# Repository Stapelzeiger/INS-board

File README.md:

INS-board
=========
This is a compact inertial navigation system (INS) board.
It is used as an autopilot for quad-copters and fixed wing aircrafts.

Main features:
-------------
 - 3-axis gyroscope
 - Two 3-axis accelerometers (one for low g and one for high g accelerations)
 - 3-axis magnetometer
 - Barometer
 - ARM controller with FPU
 - microSD card
 - USB
 - 1x CAN
 - 4x UARTs
 - 1x I2C

Finished board
--------------

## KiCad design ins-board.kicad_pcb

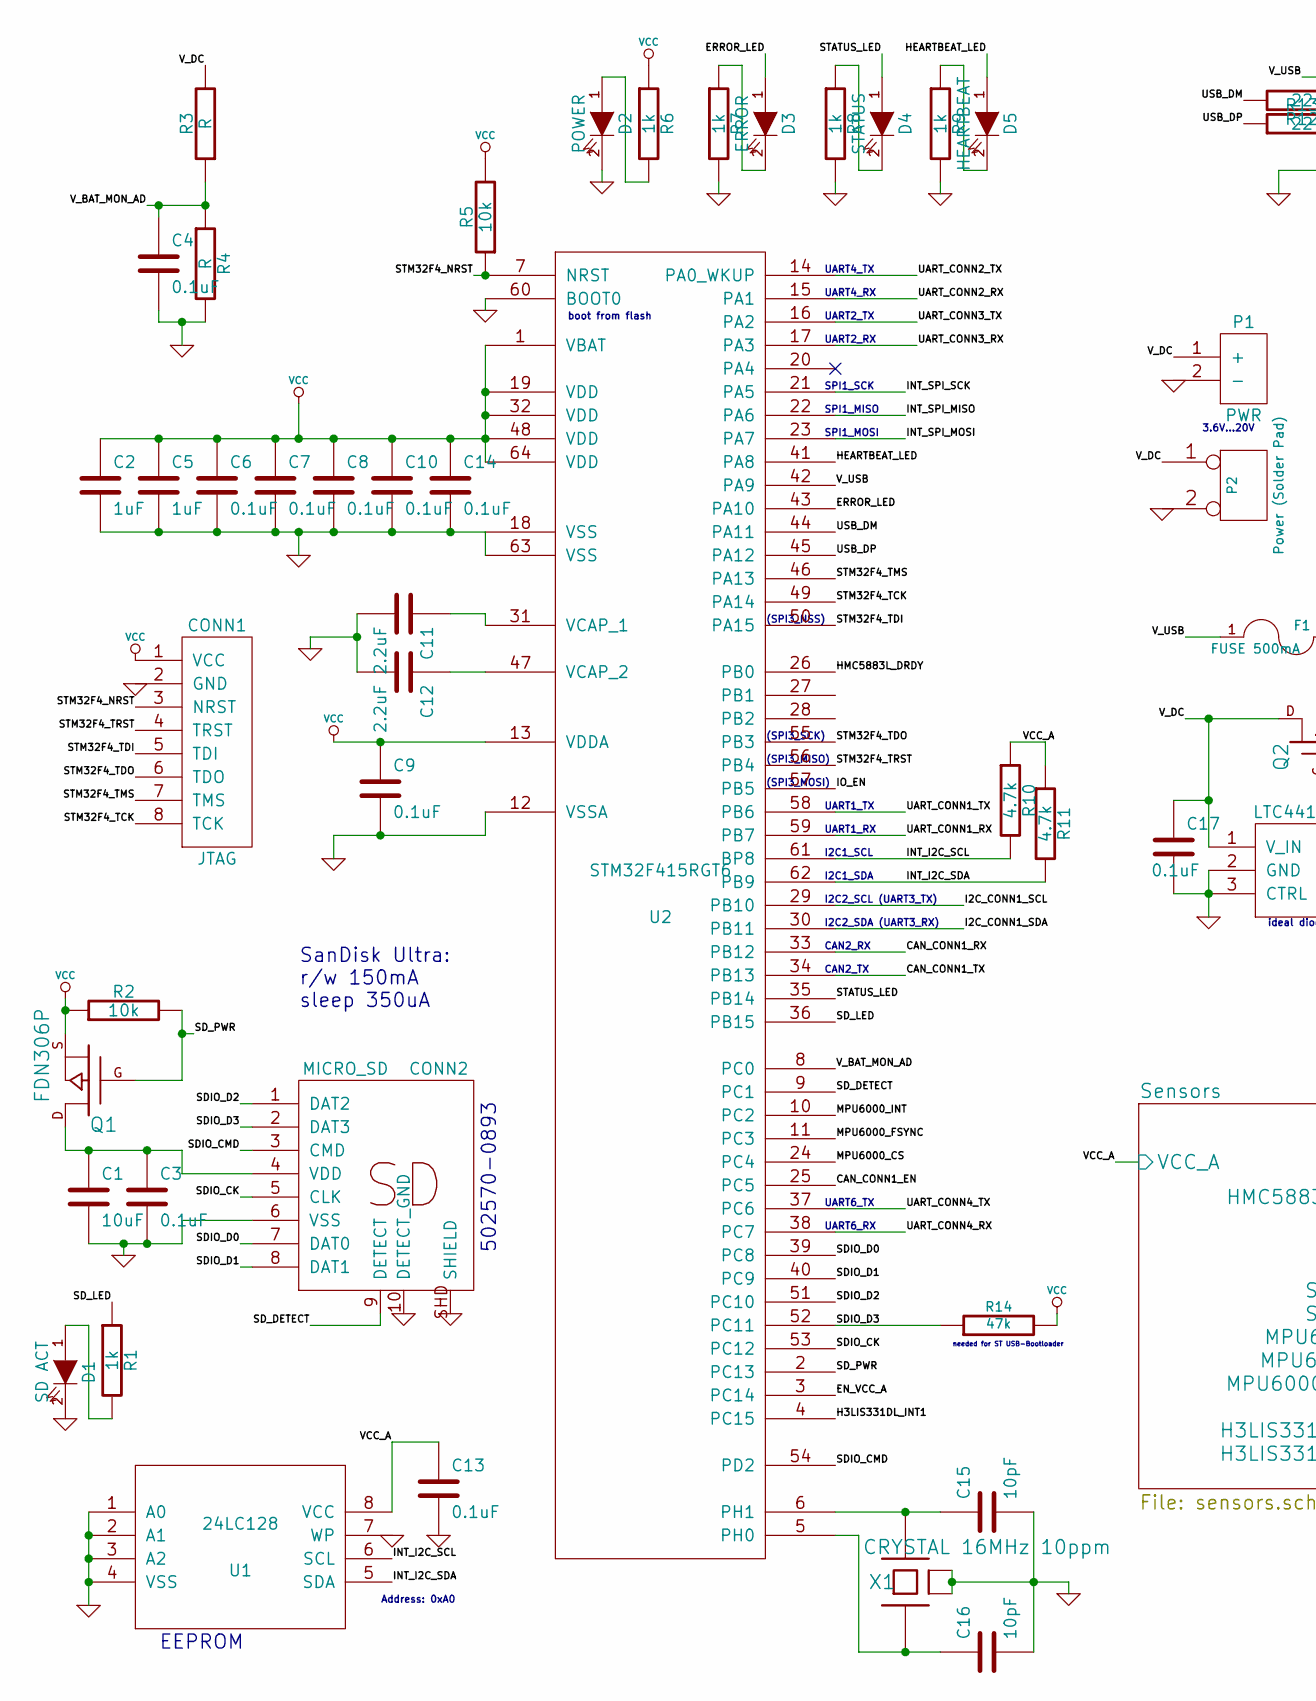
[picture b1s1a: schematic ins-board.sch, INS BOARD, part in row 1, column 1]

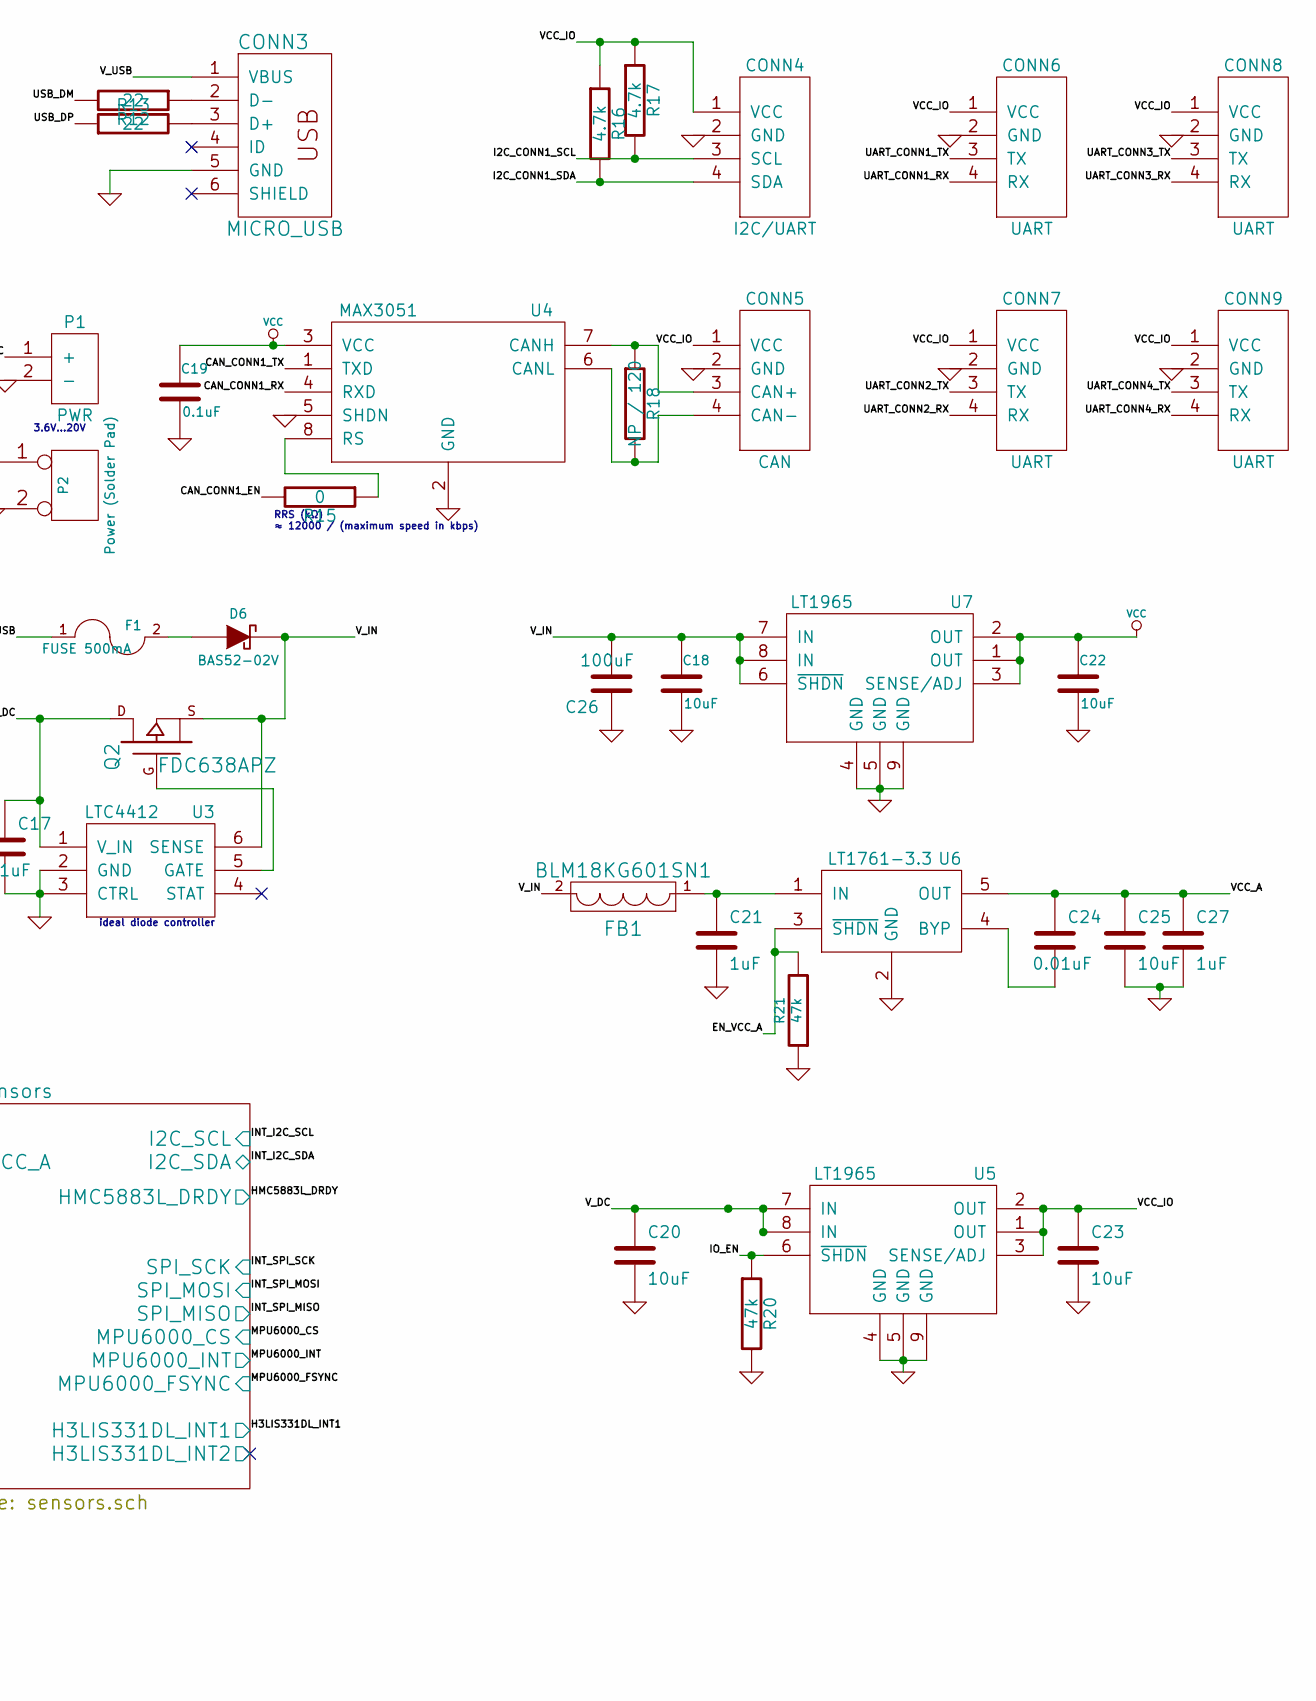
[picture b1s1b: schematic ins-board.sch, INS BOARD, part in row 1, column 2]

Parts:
C1, C20, C23, C25: 10uF
C2, C5, C21, C27: 1uF
C3, C4, C6, C7, C8, C9, C10, C13, C14, C17: 0.1uF
C11, C12: 2.2uF
C15, C16: 10pF
C18, C22: 10uF
C19: 0.1uF
C24: 0.01uF
C26: 100uF; PartNum EMK325ABJ107MM-T
CONN1: JTAG; MODULE
CONN2: MICRO_SD; MODULE
CONN3: MICRO_USB
CONN4: I2C/UART; MODULE
CONN5: CAN; MODULE
CONN6, CONN7, CONN8, CONN9: UART; MODULE
D1: SD ACT
D2: POWER
D3: ERROR
D4: STATUS
D5: HEARTBEAT
D6: BAS52-02V
F1: FUSE 500mA
FB1: BLM18KG601SN1
P1: PWR; MODULE
P2: Power (Solder Pad)
Q1: FDN306P
Q2: FDC638APZ
R1, R6, R7, R8, R9: 1k
R2, R5: 10k
R3, R4: R
R10, R11, R16, R17: 4.7k
R12, R13: 22
R14, R21: 47k
R15: 0
R18: NP / 120
R20: 47k
U1: 24LC128; MODULE
U2: STM32F415RGT6; MODULE
U3: LTC4412; MODULE
U4: MAX3051; MODULE
U5, U7: LT1965; MODULE
U6: LT1761-3.3; MODULE
X1: CRYSTAL 16MHz 10ppm

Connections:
/CAN_CONN1_EN: R15.2, U2.25 (PC5)
/CAN_CONN1_RX: U2.33 (PB12), U4.4 (RXD)
/CAN_CONN1_TX: U2.34 (PB13), U4.1 (TXD)
/EN_VCC_A: R21.2, U2.3 (PC14), U6.3 (~SHDN)
/ERROR_LED: D3.1 (A), U2.43 (PA10)
/HEARTBEAT_LED: D5.1 (A), U2.41 (PA8)
/I2C_CONN1_SCL: CONN4.3 (SCL), R17.2, U2.29 (PB10)
/I2C_CONN1_SDA: CONN4.4 (SDA), R16.2, U2.30 (PB11)
/IO_EN: R20.1, U2.57 (PB5), U5.6 (~SHDN)
/SDIO_CK: CONN2.5 (CLK), U2.53 (PC12)
/SDIO_CMD: CONN2.3 (CMD), U2.54 (PD2)
/SDIO_D0: CONN2.7 (DAT0), U2.39 (PC8)
/SDIO_D1: CONN2.8 (DAT1), U2.40 (PC9)
/SDIO_D2: CONN2.1 (DAT2), U2.51 (PC10)
/SDIO_D3: CONN2.2 (DAT3), R14.1, U2.52 (PC11)
/SD_DETECT: CONN2.9 (DETECT), U2.9 (PC1)
/SD_LED: R1.1, U2.36 (PB15)
/SD_PWR: Q1.G, R2.2, U2.2 (PC13)
/STATUS_LED: D4.1 (A), U2.35 (PB14)
/STM32F4_NRST: CONN1.3 (NRST), R5.1, U2.7 (NRST)
/STM32F4_TCK: CONN1.8 (TCK), U2.49 (PA14)
/STM32F4_TDI: CONN1.5 (TDI), U2.50 (PA15)
/STM32F4_TDO: CONN1.6 (TDO), U2.55 (PB3)
/STM32F4_TMS: CONN1.7 (TMS), U2.46 (PA13)
/STM32F4_TRST: CONN1.4 (TRST), U2.56 (PB4)
/Sensors/H3LIS331DL_INT1: U2.4 (PC15); also elsewhere on the board
/Sensors/HMC5883L_DRDY: U2.26 (PB0); also elsewhere on the board
/Sensors/I2C_SCL: R10.2, U1.6 (SCL), U2.61 (BP8); also elsewhere on the board
/Sensors/I2C_SDA: R11.2, U1.5 (SDA), U2.62 (PB9); also elsewhere on the board
/Sensors/MPU6000_CS: U2.24 (PC4); also elsewhere on the board
/Sensors/MPU6000_FSYNC: U2.11 (PC3); also elsewhere on the board
/Sensors/MPU6000_INT: U2.10 (PC2); also elsewhere on the board
/Sensors/SPI_MISO: U2.22 (PA6); also elsewhere on the board
/Sensors/SPI_MOSI: U2.23 (PA7); also elsewhere on the board
/Sensors/SPI_SCK: U2.21 (PA5); also elsewhere on the board
/Sensors/VCC_A: C13.1, C24.1, C25.1, C27.1, R10.1, R11.1, U1.8 (VCC), U6.5 (OUT); also elsewhere on the board
/UART_CONN1_RX: CONN6.4 (RX), U2.59 (PB7)
/UART_CONN1_TX: CONN6.3 (TX), U2.58 (PB6)
/UART_CONN2_RX: CONN7.4 (RX), U2.15 (PA1)
/UART_CONN2_TX: CONN7.3 (TX), U2.14 (PA0_WKUP)
/UART_CONN3_RX: CONN8.4 (RX), U2.17 (PA3)
/UART_CONN3_TX: CONN8.3 (TX), U2.16 (PA2)
/UART_CONN4_RX: CONN9.4 (RX), U2.38 (PC7)
/UART_CONN4_TX: CONN9.3 (TX), U2.37 (PC6)
/USB_DM: R12.2, U2.44 (PA11)
/USB_DP: R13.1, U2.45 (PA12)
/VCC_IO: C23.1, CONN4.1 (VCC), CONN5.1 (VCC), CONN6.1 (VCC), CONN7.1 (VCC), CONN8.1 (VCC), CONN9.1 (VCC), R16.1, R17.1, U5.1 (OUT), U5.2 (OUT), U5.3 (SENSE/ADJ)
/V_BAT_MON_AD: C4.1, R3.1, R4.1, U2.8 (PC0)
/V_DC: C17.1, C20.1, P1.1 (+), P2.1, Q2.D, R3.2, U3.1 (V_IN), U5.7 (IN), U5.8 (IN)
/V_IN: C18.1, C26.2, D6.2 (K), FB1.2, Q2.S, U3.6 (SENSE), U7.6 (~SHDN), U7.7 (IN), U7.8 (IN)
/V_USB: CONN3.1 (VBUS), F1.1, U2.42 (PA9)
GND: C1.2, C2.2, C3.2, C4.2, C5.2, C6.2, C7.2, C8.2, C9.2, C10.2, C11.2, C12.2, C13.2, C14.2, C15.2, C16.2, C17.2, C18.2, C19.2, C20.2, C21.2, C22.2, C23.2, C25.2, C26.1, C27.2, CONN1.2 (GND), CONN1.MECH (GND), CONN2.6 (VSS), CONN2.10 (DETECT_GND), CONN2.SHD (SHIELD), CONN3.5 (GND), CONN4.2 (GND), CONN4.MECH (GND), CONN5.2 (GND), CONN5.MECH (GND), CONN6.2 (GND), CONN6.MECH (GND), CONN7.2 (GND), CONN7.MECH (GND), CONN8.2 (GND), CONN8.MECH (GND), CONN9.2 (GND), CONN9.MECH (GND), D1.2 (K), D2.2 (K), P1.2 (-), P1.MECH (GND), P2.2 (PM), R4.2, R7.2, R8.2, R9.2, R20.2, R21.1, U1.1 (A0), U1.2 (A1), U1.3 (A2), U1.4 (VSS), U1.7 (WP), U2.12 (VSSA), U2.18 (VSS), U2.60 (BOOT0), U2.63 (VSS), U3.2 (GND), U3.3 (CTRL), U4.2 (GND), U4.5 (SHDN), U5.4 (GND), U5.5 (GND), U5.9 (GND), U6.2 (GND), U7.4 (GND), U7.5 (GND), U7.9 (GND), X1.2 (case), X1.4 (case); also elsewhere on the board
unnamed: D6.1 (A), F1.2
unnamed: C24.2, U6.4 (BYP)
unnamed: R15.1, U4.8 (RS)
unnamed: C11.1, U2.31 (VCAP_1)
unnamed: C12.1, U2.47 (VCAP_2)
unnamed: D2.1 (A), R6.2
unnamed: D5.2 (K), R9.1
unnamed: D4.2 (K), R8.1
unnamed: CONN3.2 (D-), R12.1
unnamed: CONN3.3 (D+), R13.2
unnamed: C16.1, U2.5 (PH0), X1.1
unnamed: C15.1, U2.6 (PH1), X1.3
unnamed: D3.2 (K), R7.1
unnamed: Q2.G, U3.5 (GATE)
unnamed: D1.1 (A), R1.2
unnamed: C21.1, FB1.1, U6.1 (IN)
unnamed: CONN5.3 (CAN+), R18.1, U4.7 (CANH)
unnamed: CONN5.4 (CAN-), R18.2, U4.6 (CANL)
unnamed: C1.1, C3.1, CONN2.4 (VDD), Q1.D
VCC: C2.1, C5.1, C6.1, C7.1, C8.1, C9.1, C10.1, C14.1, C19.1, C22.1, CONN1.1 (VCC), Q1.S, R2.1, R5.2, R6.1, R14.2, U2.1 (VBAT), U2.13 (VDDA), U2.19 (VDD), U2.32 (VDD), U2.48 (VDD), U2.64 (VDD), U4.3 (VCC), U7.1 (OUT), U7.2 (OUT), U7.3 (SENSE/ADJ)

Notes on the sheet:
ideal diode controller
Address: 0xA0
SanDisk Ultra: r/w 150mA sleep 350uA
(SPI3_MOSI)
(SPI3_MISO)
(SPI3_SCK)
(SPI3_NSS)
CAN2_TX
CAN2_RX
I2C2_SDA (UART3_RX)
I2C2_SCL (UART3_TX)
I2C1_SDA
I2C1_SCL
UART1_TX
UART1_RX
SPI1_MOSI
SPI1_MISO
SPI1_SCK
UART2_RX
UART2_TX
UART4_RX
UART4_TX
UART6_RX
UART6_TX
3.6V...20V
boot from flash
502570-0893
RRS (kΩ) ≈ 12000 / (maximum speed in kbps)
EEPROM
needed for ST USB-Bootloader

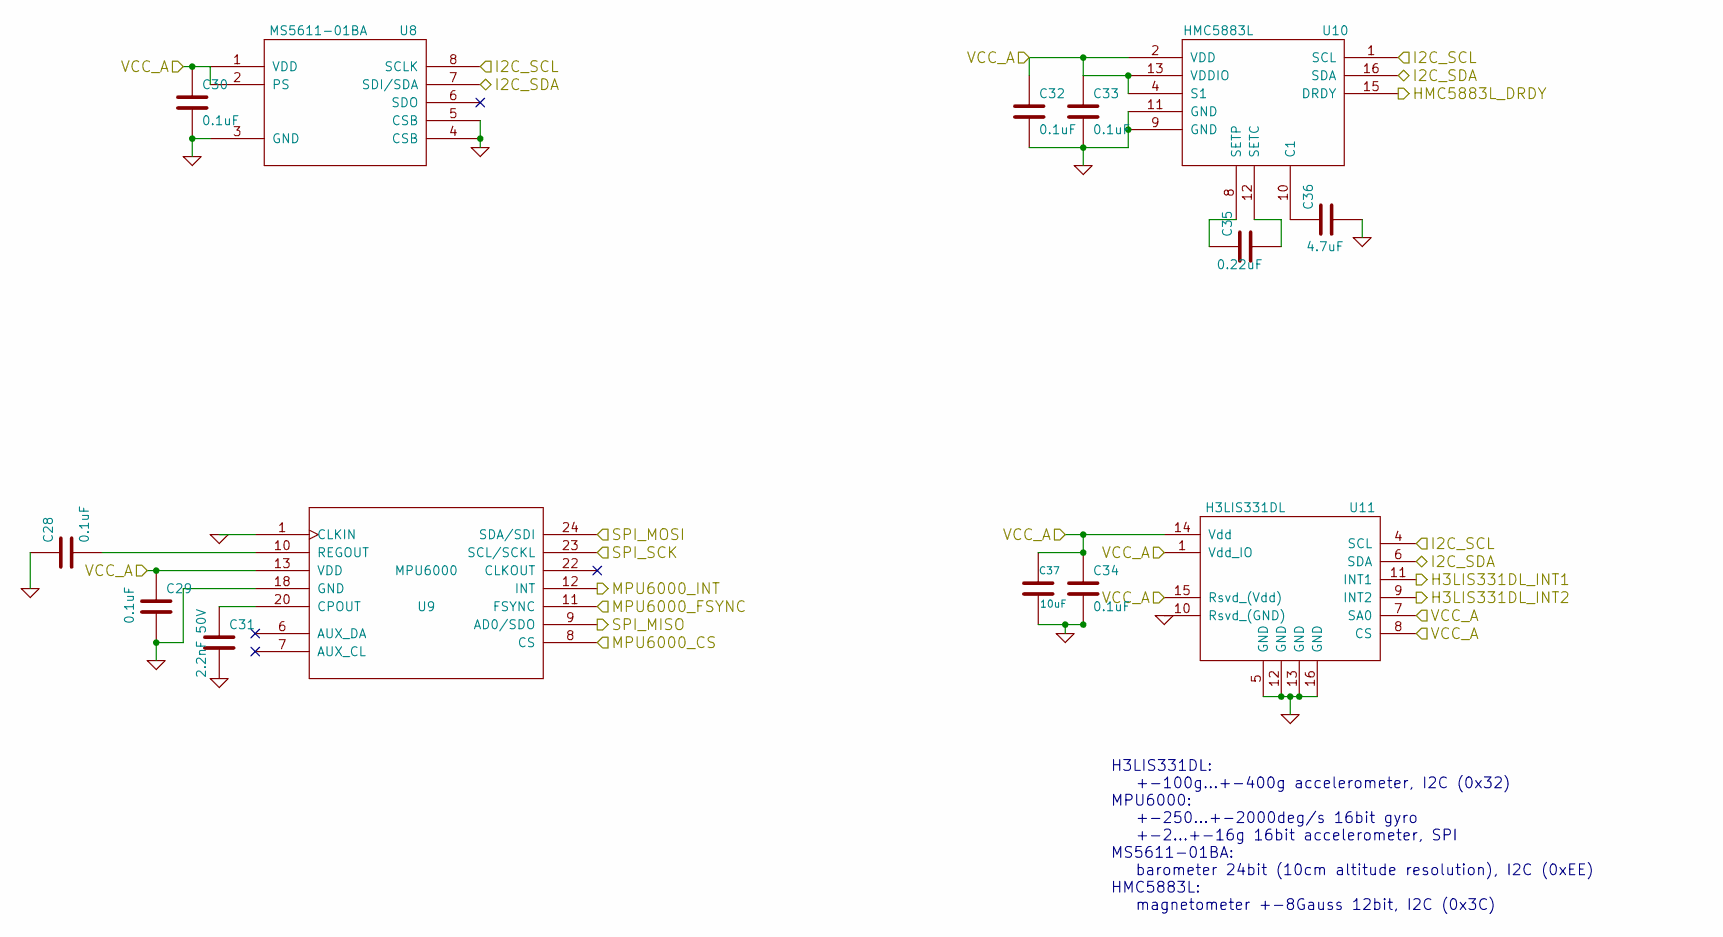
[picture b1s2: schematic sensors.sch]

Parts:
C28, C29, C30, C32, C33, C34: 0.1uF
C31: 2.2nF 50V
C35: 0.22uF
C36: 4.7uF
C37: 10uF
U8: MS5611-01BA; MODULE
U9: MPU6000; MODULE
U10: HMC5883L; MODULE
U11: H3LIS331DL; MODULE

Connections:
/Sensors/H3LIS331DL_INT1: U11.11 (INT1); also elsewhere on the board
/Sensors/HMC5883L_DRDY: U10.15 (DRDY); also elsewhere on the board
/Sensors/I2C_SCL: U8.8 (SCLK), U10.1 (SCL), U11.4 (SCL); also elsewhere on the board
/Sensors/I2C_SDA: U8.7 (SDI/SDA), U10.16 (SDA), U11.6 (SDA); also elsewhere on the board
/Sensors/MPU6000_CS: U9.8 (CS); also elsewhere on the board
/Sensors/MPU6000_FSYNC: U9.11 (FSYNC); also elsewhere on the board
/Sensors/MPU6000_INT: U9.12 (INT); also elsewhere on the board
/Sensors/SPI_MISO: U9.9 (AD0/SDO); also elsewhere on the board
/Sensors/SPI_MOSI: U9.24 (SDA/SDI); also elsewhere on the board
/Sensors/SPI_SCK: U9.23 (SCL/SCKL); also elsewhere on the board
/Sensors/VCC_A: C29.1, C30.1, C32.1, C33.1, C34.1, C37.1, U8.1 (VDD), U8.2 (PS), U9.13 (VDD), U10.2 (VDD), U10.4 (S1), U10.13 (VDDIO), U11.1 (Vdd_IO), U11.7 (SA0), U11.8 (CS), U11.14 (Vdd), U11.15 (Rsvd_(Vdd)); also elsewhere on the board
GND: C28.1, C29.2, C30.2, C31.2, C32.2, C33.2, C34.2, C36.2, C37.2, U8.3 (GND), U8.4 (CSB), U8.5 (CSB), U9.1 (CLKIN), U9.18 (GND), U10.9 (GND), U10.11 (GND), U11.5 (GND), U11.10 (Rsvd_(GND)), U11.12 (GND), U11.13 (GND), U11.16 (GND); also elsewhere on the board
unnamed: C35.1, U10.8 (SETP)
unnamed: C36.1, U10.10 (C1)
unnamed: C35.2, U10.12 (SETC)
unnamed: C31.1, U9.20 (CPOUT)
unnamed: C28.2, U9.10 (REGOUT)

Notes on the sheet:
H3LIS331DL: +-100g...+-400g accelerometer, I2C (0x32) MPU6000: +-250...+-2000deg/s 16bit gyro +-2...+-16g 16bit accelerometer, SPI MS5611-01BA: barometer 24bit (10cm altitude resolution), I2C (0xEE) HMC5883L: magnetometer +-8Gauss 12bit, I2C (0x3C)

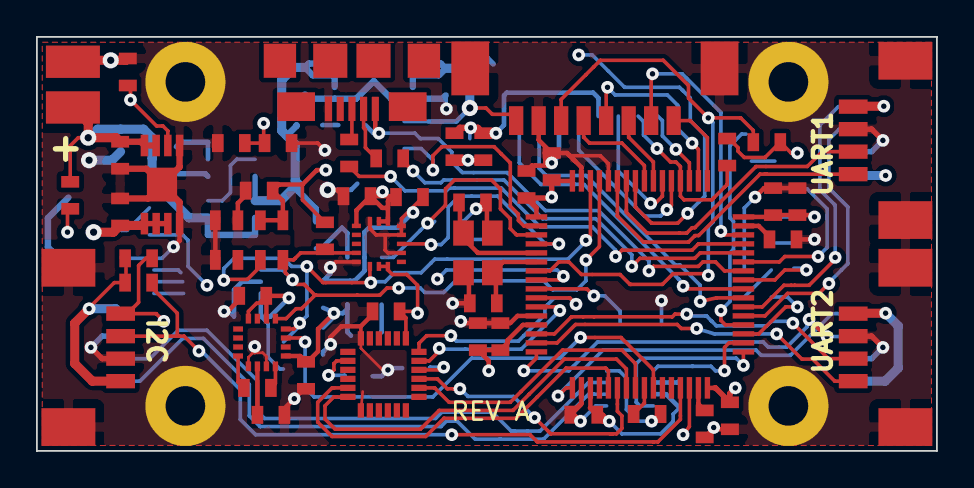
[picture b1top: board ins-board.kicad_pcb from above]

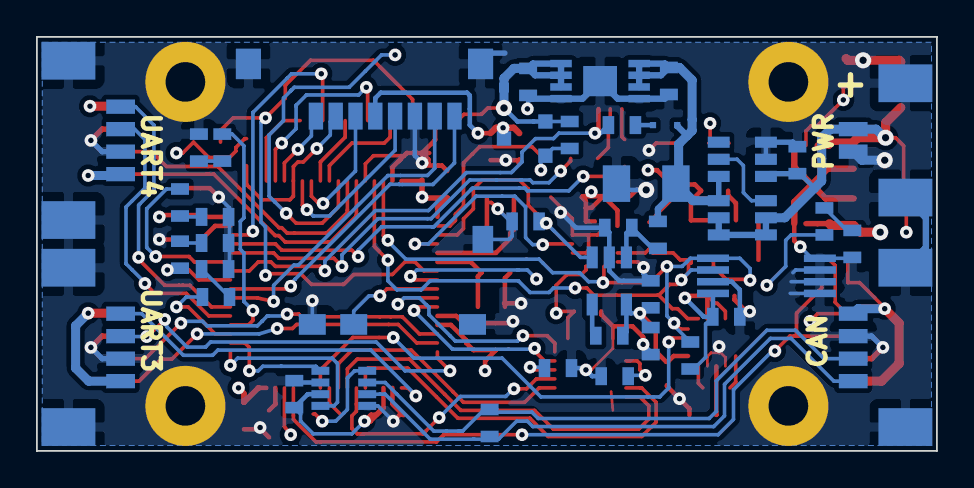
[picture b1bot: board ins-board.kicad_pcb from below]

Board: 4 copper layers, 50.0 x 23.0 mm, 94 parts (41 on the bottom side), 77 nets.

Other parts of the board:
_M2, _M2#2, _M2#3, _M2#4: VAL**; _M2

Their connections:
GND: _M2.1, _M2#2.1, _M2#3.1, _M2#4.1; also elsewhere on the board

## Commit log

2014-02-03 added a KiCad library submodule
2014-02-03 updated kicad-library
2014-02-03 updated kicad-lib
2014-02-03 add mosfet for current limiter
2014-02-06 remove usb shield connection
2014-02-07 fix errors detected by ERC
2014-02-07 replaced crystal symbol
2014-02-07 assigned most footprints to symbols
    added missing footprint library references to project file.
2014-02-07 changed shunt resistor to 68mOhm, 0603
2014-02-07 forgot netlist in prev. commit
2014-02-07 switched to renamed component and footprint libraries
2014-02-09 new power design
    - separate voltage regulator for io-connectors (powered from DC-in only)
    - removed io hot-swap controller
2014-02-09 updated annotation, added MOSFET footprints
2014-02-10 updated crystal load capacitor values
2014-02-11 updated some capacitor footprints
2014-02-11 added capacitor for max3051
2014-02-13 changed sensors power supply (VCC_IO = VCC_A)
    - all sensors and the eeprom are now powered by VCC_A
    - internal I2C pullups to VCC_A
    Reason: MS5611-01BA, HMC5883L datasheets don't specify behaviour if only vcc_io is powered / if I2C is pulled to VCC while chip is powered down
2014-02-13 corrected connection error
    U5 pin 8,6 were connected
2014-02-13 sort components
2014-02-13 change 24LC128 footprint from TSSOP to MSOP
    reason: smaller
2014-02-13 add m2 mounting holes
2014-02-14 changed SD card holder + some minor power supply changes
2014-02-14 layout
2014-02-14 layout
    90% of components
2014-02-15 add sd-card adapter, change 0603 footprints, design rules
2014-02-15 started routing
2014-02-16 routing
2014-02-16 updated library, changed component names according to new lib
    This fixes the library editor problem, where components disappear.
2014-02-16 modified sd card symbol to match footprint
2014-02-17 signal routing
2014-02-18 signal routing, all components placed
2014-02-18 solid copper connection for mounting holes
2014-02-19 power routing
2014-02-21 routing, added dimensions
2014-02-22 routing (io_en)
2014-02-24 power supply solder pad connector
2014-02-25 routing 100%
2014-02-25 optimize routing
2014-02-25 small fix, passes drc (except pad-to-pad distance for footprints)
2014-02-25 connect molex mechanical connector pads to GND
2014-02-26 keepout zones for sd card holder in gnd-fill
2014-02-26 add V_USB diode with correct footprint
2014-02-27 optimize zones
2014-02-28 replaced silkscreen with simple connector labels
2014-03-02 better GND connection of EEPROM capacitor
2014-03-05 changed eeprom package from MSOP to TSSOP
2014-03-07 center / resize all references & values
2014-03-07 added missing GND track for eeprom
2014-03-11 add doc
2014-03-15 add REV A to pcb
2014-03-17 created gerber and drill output files
2014-03-17 added soldermask layers in gerber
2014-03-25 add BOM
2014-07-10 change submodule url to github
2014-07-10 add Readme
2015-04-21 use cache lib for symbols
2015-04-21 update kicad lib
2015-04-21 reset schematic cache to new smaller symbols
2015-04-21 start fixing schematic
2015-04-21 reorganize schematic
2015-04-22 power supply
2015-04-22 fuses & diodes
2015-04-22 add FRAM
2015-04-22 schematic organization
2015-04-23 schematic layout
2015-04-25 power supply notes
2015-04-29 smaller esd protection
2015-05-02 USB ESD protection
2015-05-02 CAN pins
2015-05-02 STM32 pins
2015-05-24 schematic
2017-07-06 comments power supply changes
